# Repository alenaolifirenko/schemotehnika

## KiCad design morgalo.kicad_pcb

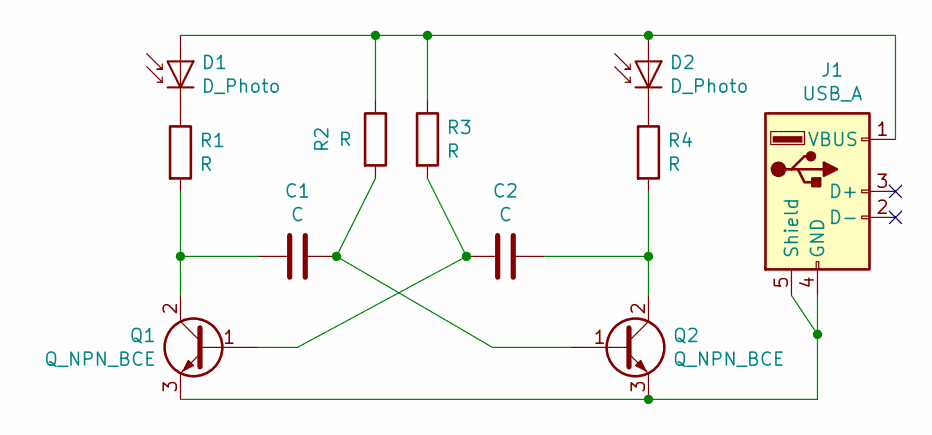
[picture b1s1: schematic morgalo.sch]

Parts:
C1, C2: C; C_0805_2012Metric_Pad1.15x1.40mm_HandSolder
D1, D2: D_Photo; D_0805_2012Metric_Pad1.15x1.40mm_HandSolder
J1: USB_A; USB_A_CNCTech_1001-011-01101_Horizontal
Q1, Q2: Q_NPN_BCE; SOT-23
R1, R2, R3, R4: R; R_0805_2012Metric_Pad1.15x1.40mm_HandSolder

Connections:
unnamed: C1.1, Q2.1 (B), R2.2
unnamed: C1.2, Q1.2 (C), R1.2
unnamed: C2.1, Q2.2 (C), R4.2
unnamed: C2.2, Q1.1 (B), R3.2
unnamed: D1.1 (K), R1.1
unnamed: D1.2 (A), D2.2 (A), J1.1 (VBUS), R2.1, R3.1
unnamed: D2.1 (K), R4.1
unnamed: J1.4 (GND), J1.5 (Shield), Q1.3 (E), Q2.3 (E)

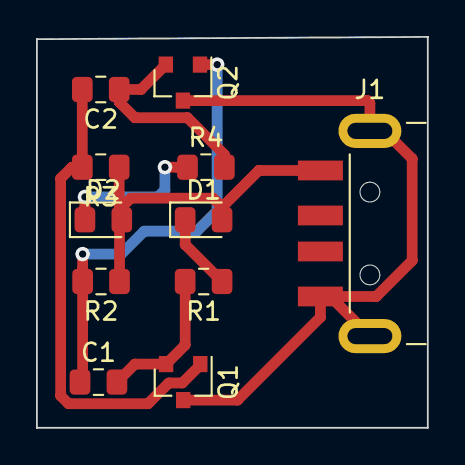
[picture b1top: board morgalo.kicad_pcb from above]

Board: 2 copper layers, 21.7 x 21.7 mm, 11 parts (0 on the bottom side), 8 nets.
